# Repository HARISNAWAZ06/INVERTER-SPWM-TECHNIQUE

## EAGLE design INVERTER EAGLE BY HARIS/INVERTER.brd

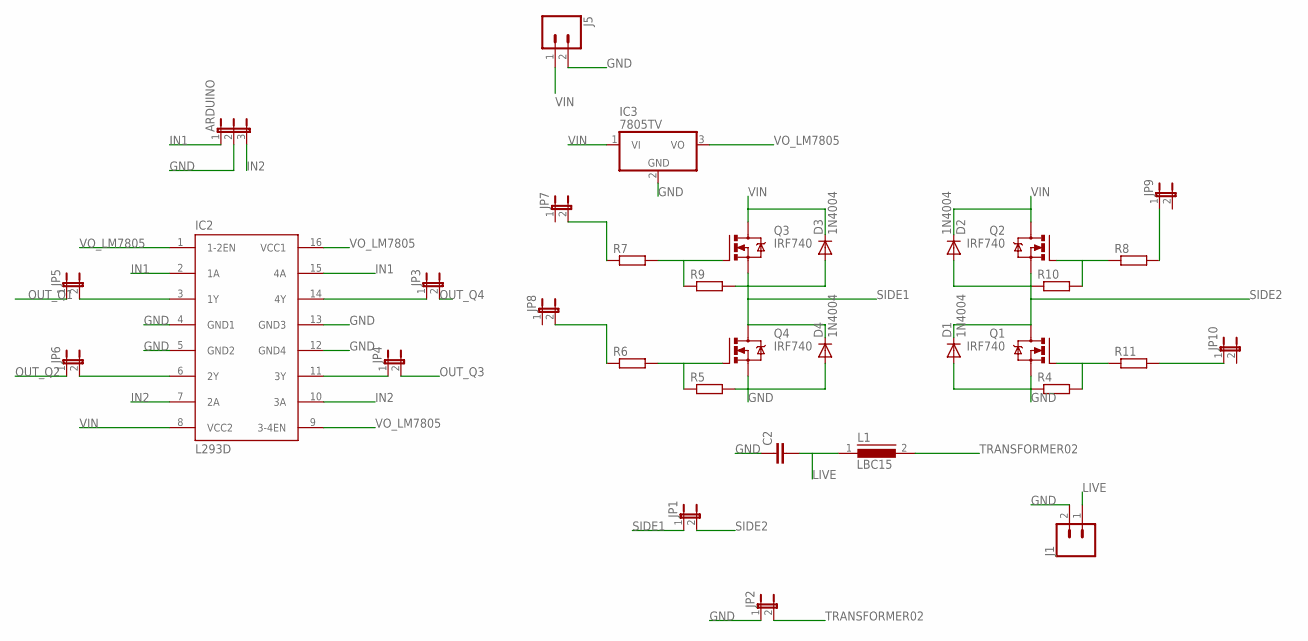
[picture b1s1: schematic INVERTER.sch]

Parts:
ARDUINO: JP2E; JP2
C2: C5/5.5; C5B5.5
D1, D2, D3, D4: 1N4004; DO41-10
IC2: L293D; DIL16
IC3: 7805TV; TO220V
J1, J5: CONN_02PTH4; 1X02_XTRA_BIG
JP1, JP2, JP3, JP4, JP5, JP6, JP7, JP8, JP9, JP10: JP1E; JP1
L1: LBC15
Q1, Q2, Q3, Q4: IRF740; TO220BV
R4, R5, R6, R7, R8, R9, R10, R11: R-EU_VMTA55; VMTA55

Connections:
GND: ARDUINO.2, C2.1, D1.A, D4.A, IC2.4 (GND1), IC2.5 (GND2), IC2.12 (GND4), IC2.13 (GND3), IC3.2 (GND), J1.2, J5.2, JP2.1, Q1.S, Q4.S, R4.1, R5.2
IN1: ARDUINO.1, IC2.2 (1A), IC2.15 (4A)
IN2: ARDUINO.3, IC2.7 (2A), IC2.10 (3A)
LIVE: C2.2, J1.1, L1.1
unnamed: IC2.3 (1Y), JP5.2
unnamed: IC2.6 (2Y), JP6.2
unnamed: Q2.G, R8.1, R10.2
unnamed: Q1.G, R4.2, R11.1
unnamed: JP7.2, R7.1
unnamed: IC2.11 (3Y), JP4.1
unnamed: Q4.G, R5.1, R6.2
unnamed: Q3.G, R7.2, R9.1
unnamed: JP8.2, R6.1
unnamed: JP9.1, R8.2
unnamed: JP10.1, R11.2
unnamed: IC2.14 (4Y), JP3.1
OUT_Q1: JP5.1
OUT_Q2: JP6.1
OUT_Q3: JP4.2
OUT_Q4: JP3.2
SIDE2: D1.C, D2.A, JP1.2, Q1.D, Q2.S, R10.1
TRANSFORMER02: JP2.2, L1.2
VIN: D2.C, D3.C, IC2.8 (VCC2), IC3.1 (VI), J5.1, Q2.D, Q3.D
VO_LM7805: IC2.1 (1-2EN), IC2.9 (3-4EN), IC2.16 (VCC1), IC3.3 (VO)

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
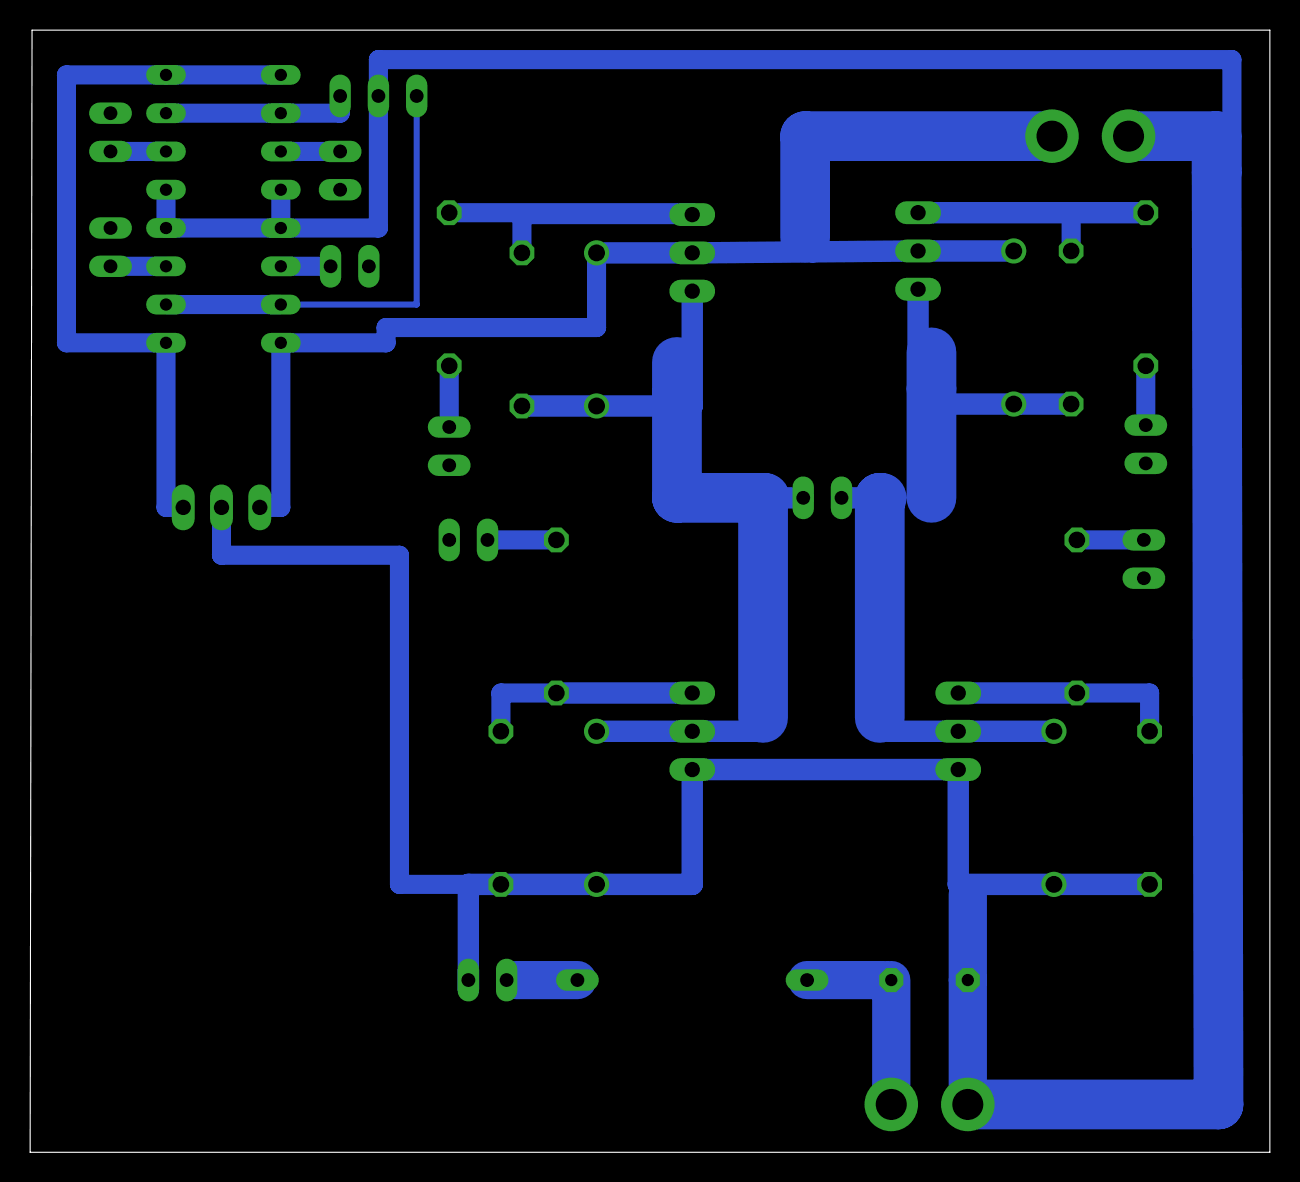
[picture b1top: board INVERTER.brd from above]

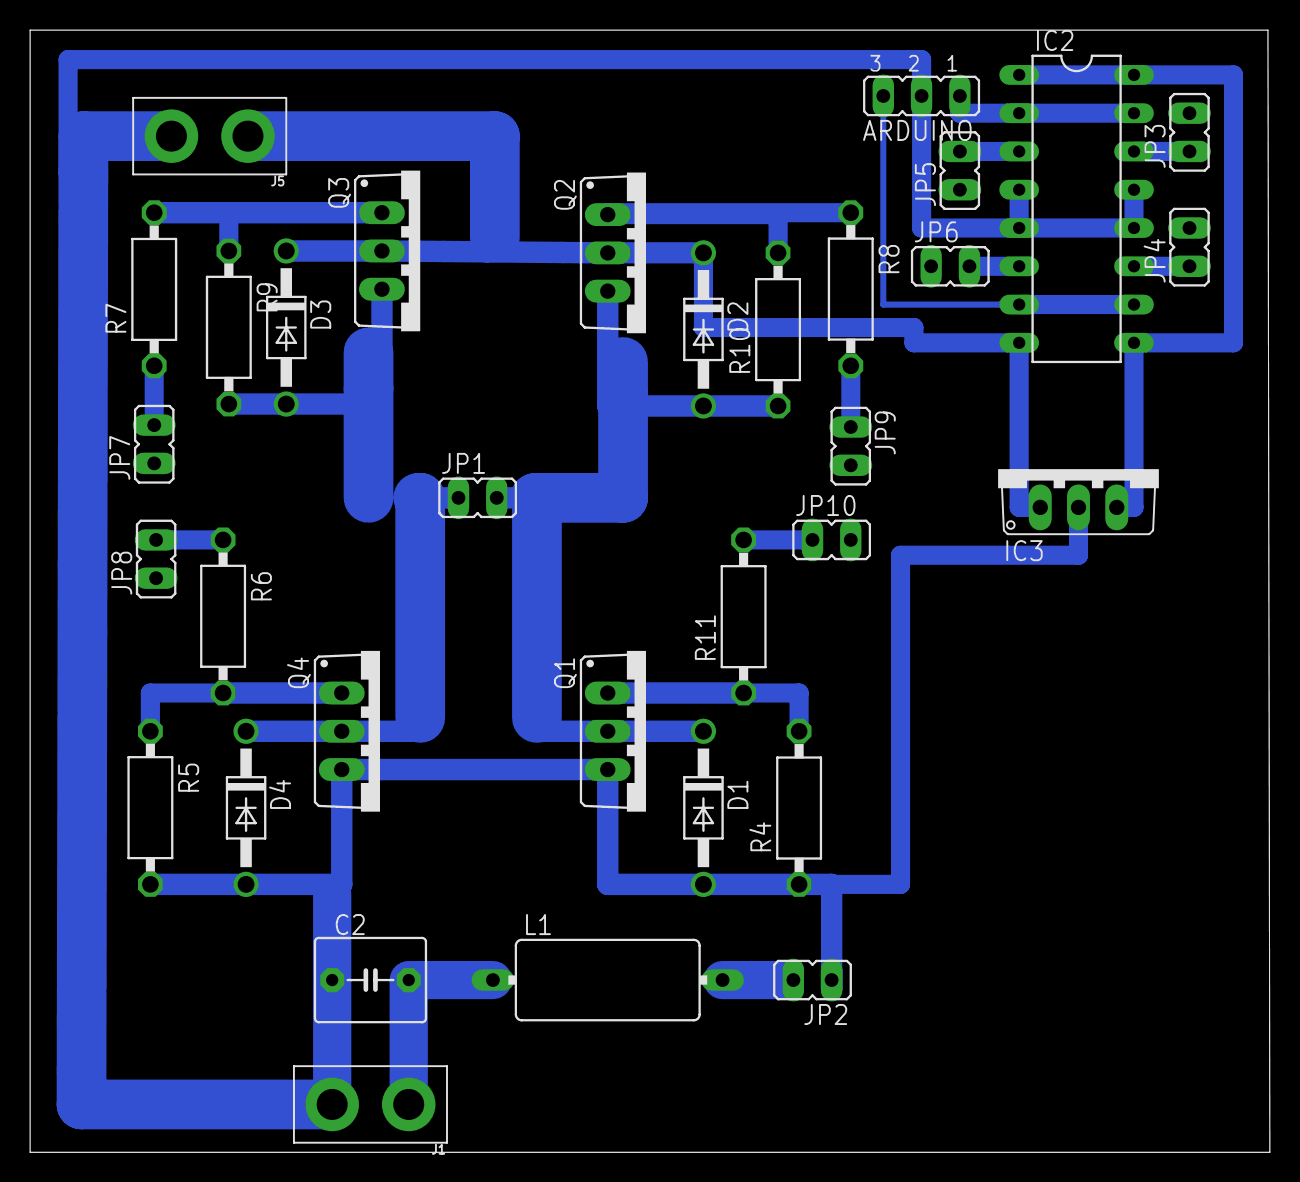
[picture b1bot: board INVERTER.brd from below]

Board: 2 copper layers, 82.3 x 74.5 mm, 33 parts (33 on the bottom side), 22 nets.

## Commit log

2022-01-24 Add files via upload
    These are the Eagle PCB design Files of DC-AC Inverter.

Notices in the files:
parts and their libraries:
SparkFun-Connectors: Licensing: Creative Commons ShareAlike 4.0 International - https://creativecommons.org/licenses/by-sa/4.0
